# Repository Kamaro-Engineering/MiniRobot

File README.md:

# MiniRobot
All construction files for a mini robot platform.

This mini robot platform was developed as an entry project for the [KAMARO](https://kamaro-engineering.de/) student group. 

(The display is not part of this project but by chance the drill holes fitted)

# CAD / Mechanics

At the moment we only provide the stl file of the robot base. On request I can provide the Free Cad file too. 

For assembly you need to 3D print the base. We did this on an ultimaker 2+.
The stepper motors we used are standard NEMA12 steppers in combination with standard rc car wheels. (Diameter will be added after I measured it)

# Circuit / Layout

The circuit schematics and layouts were done in the EAGLE layout software. The layout is partly in THT and SMD. All ICs apart from the FTDI (which is only available in SMD) are in THT, the resistors and capacitors are mostly in SMD (0805). As they are in 0805 also beginners will be able to solder them with a bit of training. (It sounds hardware that it is ;) 

The only part you have to adjust are the resistor values for the current limit of the L297. Adapt them to your maximum allowed motor current. (R7,R8 and R3,R4)

The four drill holes in the middle can be used in order to mount a raspberry pi 2 (or 3).

# Software

We provide a fully functional firmware for the Atmega48 (or 88). See the readme in the source subfolder for the serial communication protocol. (It's really simple, just 4 bytes). In most case the only thing you might have to adapt are the constants of the odomotry which is calculated with the amount of steps done by the steppers. For example in case you use a stepper with smaller steps or larger wheels you will have to adapt these constants.

See the [software readme](source/README.md)!

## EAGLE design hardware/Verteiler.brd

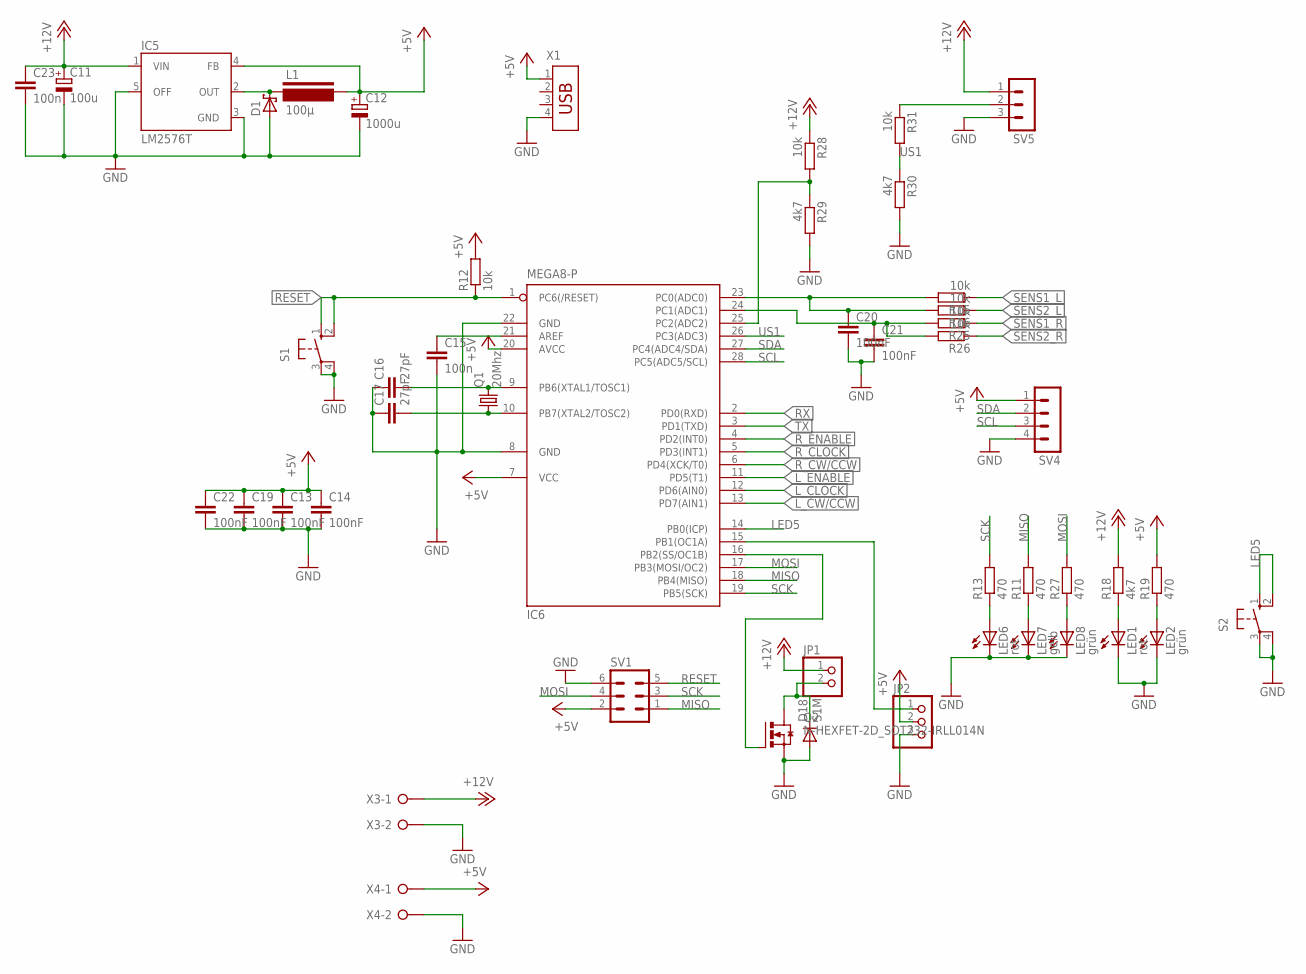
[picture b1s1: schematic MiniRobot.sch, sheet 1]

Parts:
C11: 100u; E5-10,5
C12: 1000u; E5-10,5
C13, C14, C19, C20, C21, C22: 100nF; C0805
C15, C23: 100n; C0805
C16, C17: 27pF; C0805
D1: SCHOTTKY-DIODEF126Z12; F126Z12
D18: S1M; SMA
IC5: LM2576T; TO220-5
IC6: MEGA8-P; DIL28-3
JP1: PINHD-1X2; 1X02
JP2: PINHD-1X3; 1X03
L1: 100µ; PISR
LED1, LED6: rot; CHIP-LED0805
LED2, LED8: grün; CHIP-LED0805
LED7: gelb; CHIP-LED0805
Q1: 20Mhz; CSM-7X-DU
Q2: N-HEXFET-2D_SOT232-IRLL014N; SOT223
R11, R13, R19: 470; M0805
R12, R15, R31: 10k; R0805
R16, R25, R26, R28: 10k; M0805
R18, R30: 4k7; R0805
R27: 470; R0805
R29: 4k7; M0805
S1, S2: 10-XX; B3F-10XX
SV1: ML6
SV4: MA04-1
SV5: MA03-1
X1: USB-787616; USB
X3, X4: W237-02P; W237-132

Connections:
+5V: C12.+, C13.1, C14.1, C19.1, C22.1, IC5.4 (FB), IC6.7 (VCC), IC6.20 (AVCC), JP2.2, L1.P$2, R12.2, R19.2, SV1.2, SV4.1, X1.1, X4.1; also elsewhere on the board
+12V: C11.+, C23.1, IC5.1 (VIN), JP1.1, R18.2, R28.1, SV5.1, X3.1; also elsewhere on the board
GND: C11.-, C12.-, C13.2, C14.2, C15.2, C16.1, C17.1, C19.2, C20.2, C21.2, C22.2, C23.2, D1.A, D18.A, IC5.3 (GND), IC5.5 (OFF), IC6.8 (GND), IC6.22 (GND), JP2.3, LED1.C, LED2.C, LED6.C, LED7.C, LED8.C, Q2.3 (S), R29.2, R30.2, S1.3, S1.4 (P1), S2.3, S2.4 (P1), SV1.6, SV4.4, SV5.3, X1.4, X3.2, X4.2; also elsewhere on the board
LED5: IC6.14 (PB0(ICP)), S2.1 (S), S2.2 (S1)
L_CLOCK: IC6.12 (PD6(AIN0)); also elsewhere on the board
L_CW/CCW: IC6.13 (PD7(AIN1)); also elsewhere on the board
L_ENABLE: IC6.11 (PD5(T1)); also elsewhere on the board
MISO: IC6.18 (PB4(MISO)), R11.2, SV1.1
MOSI: IC6.17 (PB3(MOSI/OC2)), R27.2, SV1.4
unnamed: LED8.A, R27.1
unnamed: C21.1, IC6.24 (PC1(ADC1)), R25.2, R26.2
unnamed: C15.1, IC6.21 (AREF)
unnamed: C16.2, IC6.9 (PB6(XTAL1/TOSC1)), Q1.2
unnamed: D1.C, IC5.2 (OUT), L1.P$1
unnamed: IC6.25 (PC2(ADC2)), R28.2, R29.1
unnamed: C17.2, IC6.10 (PB7(XTAL2/TOSC2)), Q1.1
unnamed: C20.1, IC6.23 (PC0(ADC0)), R15.2, R16.2
unnamed: LED1.A, R18.1
unnamed: LED2.A, R19.1
unnamed: LED6.A, R13.1
unnamed: LED7.A, R11.1
unnamed: R31.1, SV5.2
unnamed: D18.C, JP1.2, Q2.2 (D), Q2.4 (D)
unnamed: IC6.16 (PB2(SS/OC1B)), Q2.1 (G)
unnamed: IC6.15 (PB1(OC1A)), JP2.1
RESET: IC6.1 (PC6(/RESET)), R12.1, S1.1 (S), S1.2 (S1), SV1.5; also elsewhere on the board
RX: IC6.2 (PD0(RXD)); also elsewhere on the board
R_CLOCK: IC6.5 (PD3(INT1)); also elsewhere on the board
R_CW/CCW: IC6.6 (PD4(XCK/T0)); also elsewhere on the board
R_ENABLE: IC6.4 (PD2(INT0)); also elsewhere on the board
SCK: IC6.19 (PB5(SCK)), R13.2, SV1.3
SCL: IC6.28 (PC5(ADC5/SCL)), SV4.3
SDA: IC6.27 (PC4(ADC4/SDA)), SV4.2
SENS1_L: R15.1; also elsewhere on the board
SENS1_R: R25.1; also elsewhere on the board
SENS2_L: R16.1; also elsewhere on the board
SENS2_R: R26.1; also elsewhere on the board
TX: IC6.3 (PD1(TXD)); also elsewhere on the board
US1: IC6.26 (PC3(ADC3)), R30.1, R31.2

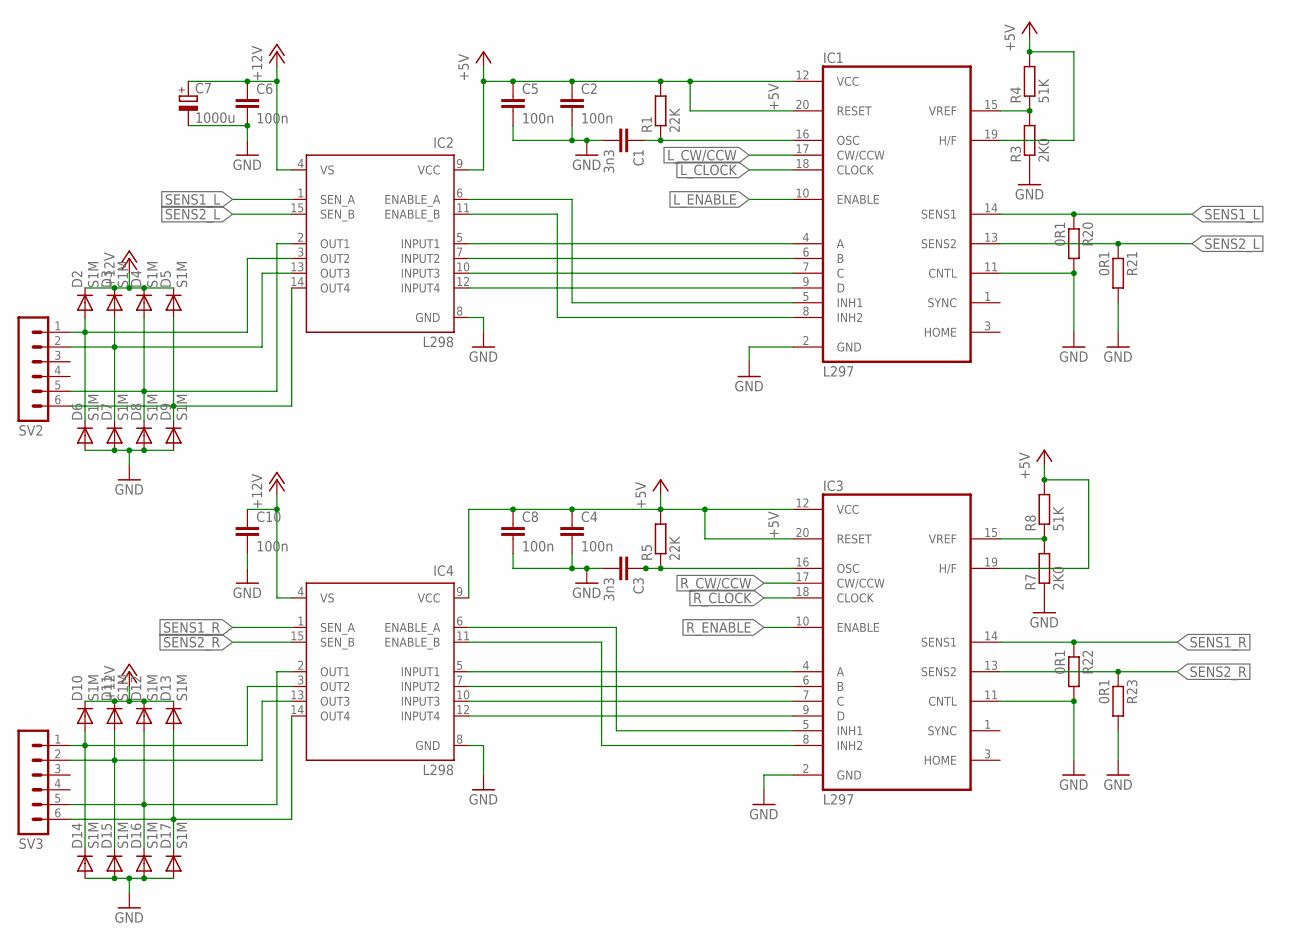
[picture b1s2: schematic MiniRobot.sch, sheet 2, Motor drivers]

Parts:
C1, C3: 3n3; C0805
C2, C4, C5, C6, C8, C10: 100n; C0805
C7: 1000u; E5-10,5
D2, D3, D4, D5, D6, D7, D8, D9, D10, D11, D12, D13, D14, D15, D16, D17: S1M; SMA
IC1, IC3: L297; DIL20
IC2, IC4: L298; MULTIWATT-15
R1, R5: 22K; R0805
R3, R7: 2K0; R0805
R4, R8: 51K; R0805
R20, R21, R22, R23: 0R1; P0613/15
SV2, SV3: MA06-1

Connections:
+5V: C2.1, C4.1, C5.1, C8.1, IC1.12 (VCC), IC1.19 (H/F), IC1.20 (RESET), IC2.9 (VCC), IC3.12 (VCC), IC3.19 (H/F), IC3.20 (RESET), IC4.9 (VCC), R1.2, R4.2, R5.2, R8.2; also elsewhere on the board
+12V: C6.1, C7.+, C10.1, D2.C, D3.C, D4.C, D5.C, D10.C, D11.C, D12.C, D13.C, IC2.4 (VS), IC4.4 (VS); also elsewhere on the board
GND: C1.2, C2.2, C3.2, C4.2, C5.2, C6.2, C7.-, C8.2, C10.2, D6.A, D7.A, D8.A, D9.A, D14.A, D15.A, D16.A, D17.A, IC1.2 (GND), IC1.11 (CNTL), IC2.8 (GND), IC3.2 (GND), IC3.11 (CNTL), IC4.8 (GND), R3.1, R7.1, R20.2, R21.2, R22.2, R23.2; also elsewhere on the board
L_CLOCK: IC1.18 (CLOCK); also elsewhere on the board
L_CW/CCW: IC1.17 (CW/CCW); also elsewhere on the board
L_ENABLE: IC1.10 (ENABLE); also elsewhere on the board
unnamed: C1.1, IC1.16 (OSC), R1.1
unnamed: IC1.4 (A), IC2.5 (INPUT1)
unnamed: IC1.6 (B), IC2.7 (INPUT2)
unnamed: IC1.7 (C), IC2.10 (INPUT3)
unnamed: C3.1, IC3.16 (OSC), R5.1
unnamed: IC3.6 (B), IC4.7 (INPUT2)
unnamed: IC1.9 (D), IC2.12 (INPUT4)
unnamed: IC1.5 (INH1), IC2.6 (ENABLE_A)
unnamed: IC1.15 (VREF), R3.2, R4.1
unnamed: D4.A, D8.C, IC2.2 (OUT1), SV2.5
unnamed: IC3.4 (A), IC4.5 (INPUT1)
unnamed: IC3.7 (C), IC4.10 (INPUT3)
unnamed: IC3.9 (D), IC4.12 (INPUT4)
unnamed: IC3.15 (VREF), R7.2, R8.1
unnamed: IC3.5 (INH1), IC4.6 (ENABLE_A)
unnamed: IC1.8 (INH2), IC2.11 (ENABLE_B)
unnamed: D2.A, D6.C, IC2.3 (OUT2), SV2.1
unnamed: D3.A, D7.C, IC2.13 (OUT3), SV2.2
unnamed: D5.A, D9.C, IC2.14 (OUT4), SV2.6
unnamed: IC3.8 (INH2), IC4.11 (ENABLE_B)
unnamed: D10.A, D14.C, IC4.3 (OUT2), SV3.1
unnamed: D12.A, D16.C, IC4.2 (OUT1), SV3.5
unnamed: D13.A, D17.C, IC4.14 (OUT4), SV3.6
unnamed: D11.A, D15.C, IC4.13 (OUT3), SV3.2
R_CLOCK: IC3.18 (CLOCK); also elsewhere on the board
R_CW/CCW: IC3.17 (CW/CCW); also elsewhere on the board
R_ENABLE: IC3.10 (ENABLE); also elsewhere on the board
SENS1_L: IC1.14 (SENS1), IC2.1 (SEN_A), R20.1; also elsewhere on the board
SENS1_R: IC3.14 (SENS1), IC4.1 (SEN_A), R22.1; also elsewhere on the board
SENS2_L: IC1.13 (SENS2), IC2.15 (SEN_B), R21.1; also elsewhere on the board
SENS2_R: IC3.13 (SENS2), IC4.15 (SEN_B), R23.1; also elsewhere on the board

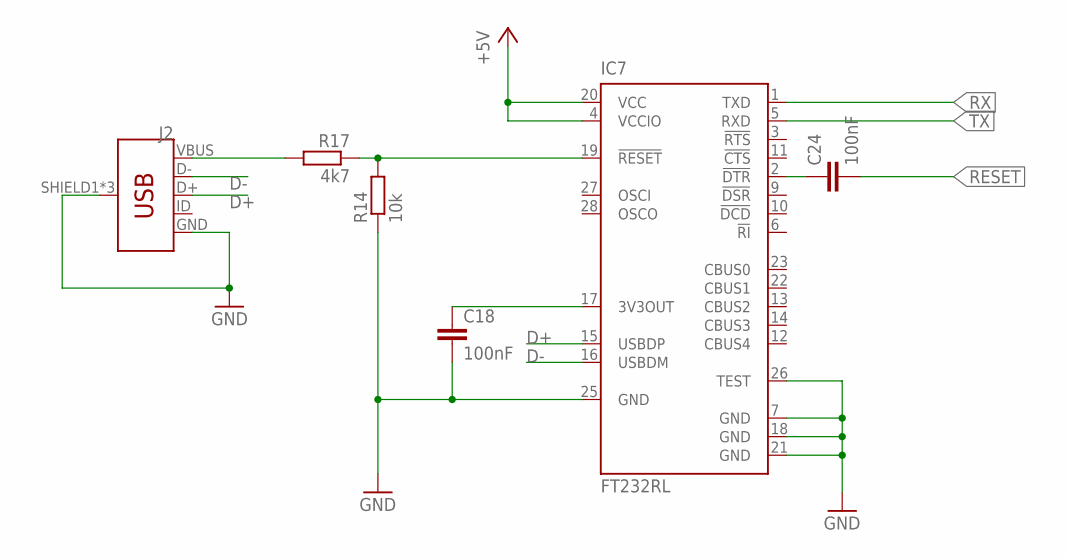
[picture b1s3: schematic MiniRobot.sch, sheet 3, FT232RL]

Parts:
C18, C24: 100nF; C0805
IC7: FT232RL; SSOP28
J2: USB_MICRO-B_FEMALE-SMT; USB-B-MICRO-SMD
R14: 10k; M0805
R17: 4k7; M0805

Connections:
+5V: IC7.4 (VCCIO), IC7.20 (VCC); also elsewhere on the board
D+: IC7.15 (USBDP), J2.D+
D-: IC7.16 (USBDM), J2.D-
GND: C18.2, IC7.7 (GND), IC7.18 (GND), IC7.21 (GND), IC7.25 (GND), IC7.26 (TEST), J2.GND, J2.SHIELD1 (SHIELD), J2.SHIELD2 (SHIELD), J2.SHIELD3 (SHIELD), R14.1; also elsewhere on the board
unnamed: J2.VBUS, R17.2
unnamed: IC7.19 (!RESET), R14.2, R17.1
unnamed: C18.1, IC7.17 (3V3OUT)
unnamed: C24.1, IC7.2 (!DTR)
RESET: C24.2; also elsewhere on the board
RX: IC7.1 (TXD); also elsewhere on the board
TX: IC7.5 (RXD); also elsewhere on the board

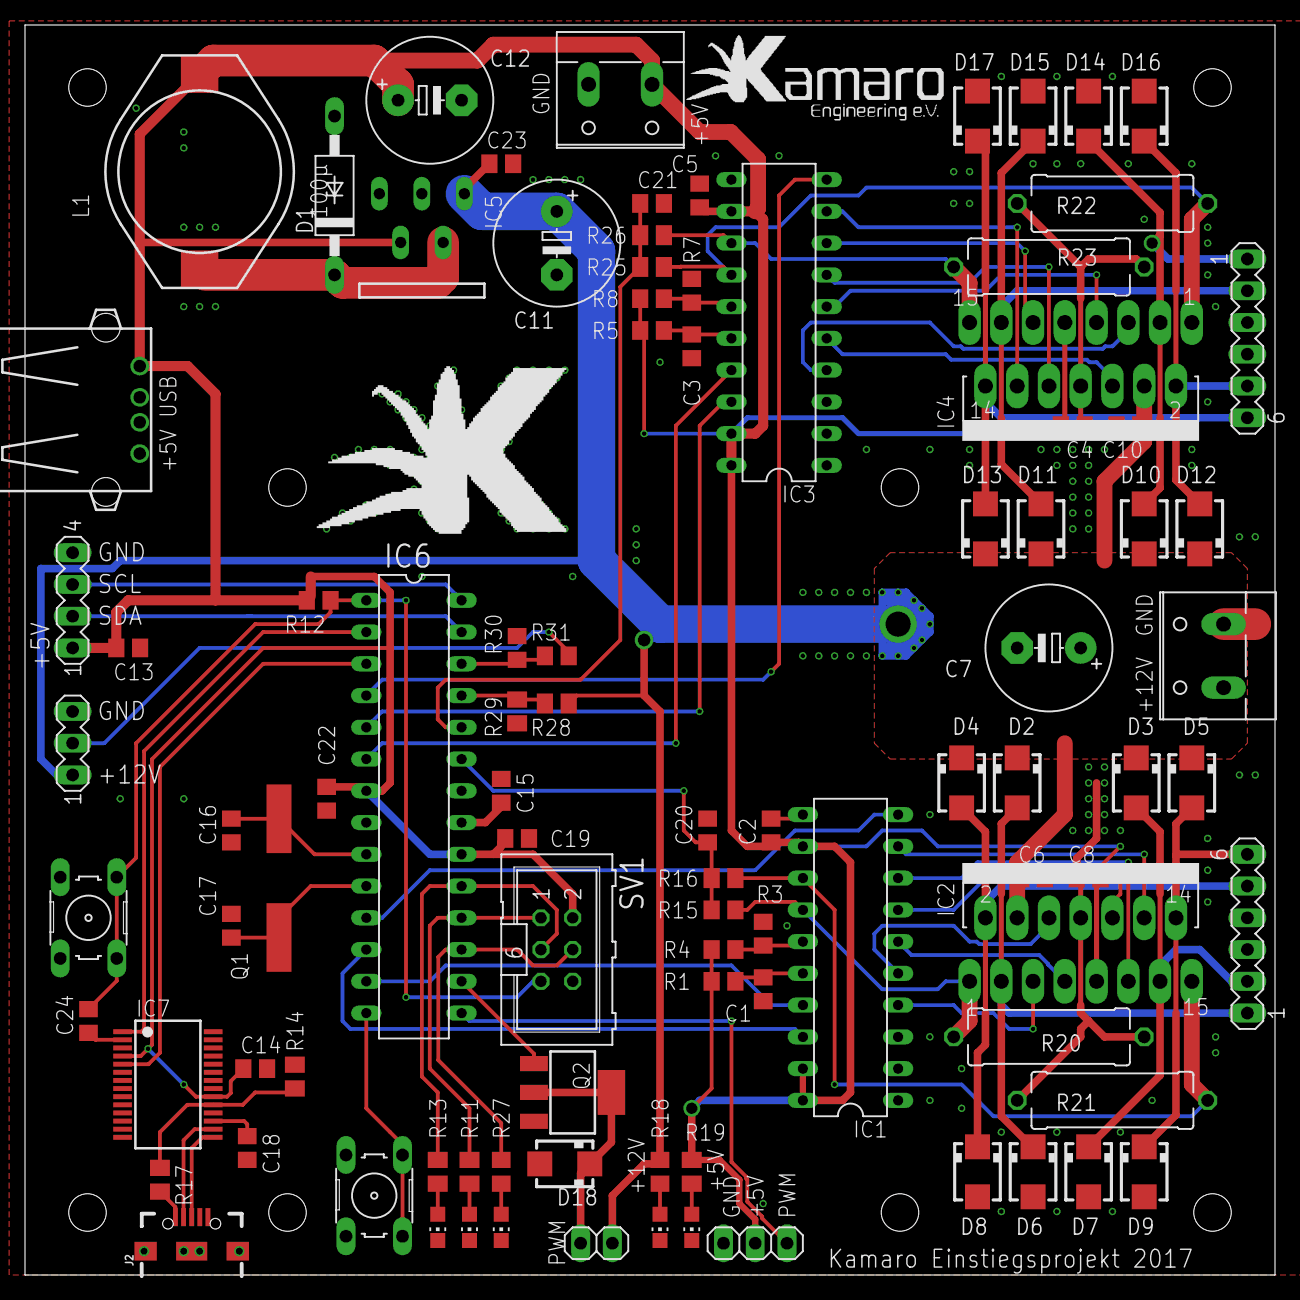
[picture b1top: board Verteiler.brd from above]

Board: 2 copper layers, 100.0 x 100.0 mm, 95 parts (0 on the bottom side), 69 nets.

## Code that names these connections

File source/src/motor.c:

/*
 * Copyright 2017 <Lennart Nachtigall, Friedolin Gröger> <firesurfer127@gmail.com, gfrodo@gmx.de>
 *
 * Licensed under the Apache License, Version 2.0 (the "License");
 * you may not use this file except in compliance with the License.
 * You may obtain a copy of the License at
 *
 *     http://www.apache.org/licenses/LICENSE-2.0
 *
 * Unless required by applicable law or agreed to in writing, software
 * distributed under the License is distributed on an "AS IS" BASIS,
 * WITHOUT WARRANTIES OR CONDITIONS OF ANY KIND, either express or implied.
 * See the License for the specific language governing permissions and
 * limitations under the License.
 *
 */


#include <avr/io.h>
#include <avr/interrupt.h>
#include "motor.h"

#define PIN_R_ENABLE 2
#define PIN_R_CLOCK  3
#define PIN_R_DIR    4
#define PIN_L_ENABLE 5
#define PIN_L_CLOCK  6
#define PIN_L_DIR    7

#define PORTMOT PORTD
#define PINMOT  PIND
#define DDRMOT  DDRD

// To invert direction if one motor is going backwards
#define DIR_INV_R 0
#define DIR_INV_L 0


uint16_t count_r = 0;
uint16_t count_l = 0;

int16_t speed_r = 0;
int16_t speed_l = 0;

volatile int16_t odom_r = 0;
volatile int16_t odom_l = 0;

void set_motor_enable(uint8_t enable)
{
    if (enable)
        PORTMOT |= (1 << PIN_R_ENABLE) | (1 << PIN_L_ENABLE);
    else
        PORTMOT &= ~(1 << PIN_R_ENABLE) & ~(1 << PIN_L_ENABLE);
}
void set_motor_enable_r(uint8_t enable)
{
    if (enable)
        PORTMOT |= (1 << PIN_R_ENABLE) ;
    else
        PORTMOT &= ~(1 << PIN_R_ENABLE) ;
}
void set_motor_enable_l(uint8_t enable)
{
    if (enable)
        PORTMOT |= (1 << PIN_L_ENABLE);
    else
        PORTMOT &= ~(1 << PIN_L_ENABLE);
}

void motor_init()
{
    TCCR0B = (1 << CS01) | (1 << CS00); // Prescaler 64
    TIMSK0 = (1 << TOIE0);            // Overflow interrupt enable
    //TCCR2B = (1<<CS22);               // Prescaler 64
    //TIMSK2 = (1<<TOIE2);              // Overflow interrupt enable
    DDRMOT |= (1 << PIN_R_ENABLE) | (1 << PIN_R_CLOCK) | (1 << PIN_R_DIR)
              | (1 << PIN_L_ENABLE) | (1 << PIN_L_CLOCK) | (1 << PIN_L_DIR);
    //PORTMOT |= (1 << PIN_R_ENABLE) | (1 << PIN_L_ENABLE);
}

void motor_speed_l(int16_t speed)
{
    speed_l = speed;
}
void motor_speed_r(int16_t speed)
{
    speed_r = speed;
}
int16_t get_odom_r()
{
    return odom_r;
}
int16_t get_odom_l()
{
    return odom_l;
}

ISR(TIMER0_OVF_vect)
{
    count_r += abs(speed_r);
    if (count_r & 0x8000) { //on "overflow"
        count_r &= 0x7FFF; //do the overflow
        if (speed_r > 0) {
            odom_r += 1; //count ticks
            if (DIR_INV_R) PORTMOT &= ~(1 << PIN_R_DIR); //set direction pin
            else PORTMOT |= (1 << PIN_R_DIR);
        } else {
            odom_r -= 1;
            if (DIR_INV_R) PORTMOT |= (1 << PIN_R_DIR);
            else PORTMOT &= ~(1 << PIN_R_DIR);
        }
        PINMOT = (1 << PIN_R_CLOCK); //toggle frequency pin
    }
    count_l += abs(speed_l);
    if (count_l & 0x8000) { //on "overflow"
        count_l &= 0x7FFF; //do the overflow
        if (speed_l > 0) {
            odom_l += 1; //count ticks
            if (DIR_INV_L) PORTMOT &= ~(1 << PIN_L_DIR); //set direction pin
            else PORTMOT |= (1 << PIN_L_DIR);
        } else {
            odom_l -= 1;
            if (DIR_INV_L) PORTMOT |= (1 << PIN_L_DIR);
            else PORTMOT &= ~(1 << PIN_L_DIR);
        }
        PINMOT = (1 << PIN_L_CLOCK); //toggle frequency pin
    }
}

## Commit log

2017-10-25 added cad file
2017-10-25 added source
2017-10-25 set date to 2017
2017-10-25 added schematic and layout of board
2017-10-26 moved circuit schematics into folder. updated readme
2017-10-26 added images
2017-10-26 fixed readme
2017-10-26 really fixed readme
2017-10-26 rearanged readme

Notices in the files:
parts and their libraries:
SparkFun-Connectors: Licensing: Creative Commons ShareAlike 4.0 International - https://creativecommons.org/licenses/by-sa/4.0
